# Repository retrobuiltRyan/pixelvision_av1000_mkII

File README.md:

# PixelVision_AV-1000_MkII

Desktop sized multi-format video display monitor for HDMI and legacy analog video input with built-in speakers.
Watch the video: (assembly section @14:51) <br>
 ## https://youtu.be/MTYouu-5v1Q <br> 
 <br>
## Hardware Overview

| Specification | Details |
|---|---|
| Viewable Size | 9.7” [4:3 ratio] |
| Input Signals | HDMI [2048×1536]; VGA [1920×1080]; YPbPr, S-video, Composite [480p] |
| Audio Input/Output | Analog 3.5mm stereo |
| Speaker Output | Stereo (5 watt) |
| Power Consumption | 10 watts (2w standby) |
| Dimensions (W × H × D) | 248 × 205 × 192 mm (9.76 × 8.07 × 7.56 inches) |
| Weight | 1350 g |

### IPS [iPad 3/4] Panel Details

| Specification | Details |
|---|---|
| Pixel Density | 264 PPI |
| View Angle | 89/89/89/89 (Typ.) (CR ≥ 10) |
| Frequency | 60 Hz |
| Panel Type / Model | a-Si TFT-LCD, LCM / LP097QX1-SPC1 |
| Brightness | 440 cd/m² |

## Electrical Diagram
 <br>

## Bill of Materials
| Item | Description | Vendor Link | Cost/each (USD) | Qty | Line Total (USD) |
|------|-------------|-------------|----------------:|----:|-----------------:|
| 1 alt | Speaker Dayton Audio CE32A-4 1-1/4" | [parts-express](https://www.parts-express.com/Dayton-Audio-CE32A-4-1-1-4-Mini-Speaker-4-Ohm-285-103) | 3.58 | 2 | $7.16 |
| 1 | Speaker Visaton FR7-4 2.5" | [parts-express](https://www.parts-express.com/Visaton-FR7-4-2-1-2-Full-Range-Driver-4-Ohm-292-638) | 6.47 | 2 | $12.94 |
| 2 | LCD 9.7" 2048×1536 HDMI | [aliexpress](https://www.aliexpress.us/item/3256803412961622.html) | 50.60 | 1 | $50.60 |
| 3 | Scan Line Converter | [aliexpress](https://www.aliexpress.us/item/3256805577379481.html) | 47.64 | 1 | $47.64 |
| 4 | M2.6 × 10mm Thread Forming Screw | [aliexpress]([#](https://www.aliexpress.us/item/3256807955659503.html)) | 0.04 | 70 | $2.80 |
| 5 | M3 × 6mm Button Head Screws | any | 0.03 | 3 | $0.09 |
| 6 | M3 × 11mm F/F Standoff | any | 0.10 | 3 | $0.30 |
| 7 | Filament, 1 gram PLA | any | 0.02 | 877 | $17.54 |
| 8 | Audio Amp PAM8406 | [aliexpress](https://www.aliexpress.us/item/3256807320222817.html) | 6.48 | 1 | $6.48 |
| 9 | M6 × 30 Steel Phillips Flat Head Screw | [mcmaster](https://www.mcmaster.com/91420A438/) | 0.13 | 1 | $0.13 |
| 10 | M6 Nylon Lock Nut | [mcmaster](https://www.mcmaster.com/90631A114/) | 0.08 | 1 | $0.08 |
| 11 | HDMI Super Slim Cable, 1 ft | [parts-express](https://www.parts-express.com/Audtek-TS1-1-ft.-Super-Slim-Ultra-HD-HDMI-2.0-Cable-4K60-Hz-HDR-YCbCr-444-18-Gbps-180-1318) | 3.97 | 1 | $3.97 |
| 12 | Audio Cable, Slim, 1 ft, 3.5mm | [parts-express](https://www.parts-express.com/3.5mm-Male-to-Male-Slim-Plug-Shielded-Audio-Cable-1-ft.-240-051) | 1.59 | 1 | $1.59 |
| 13 | DC Power Jack, Panel Mount (2.1 × 5.5mm) | [aliexpress](https://www.aliexpress.us/item/3256808307457555.html) | 0.45 | 2 | $0.90 |
| 14 | Rocker Switch panel mount (19 x 13mm) | [parts-express](https://www.parts-express.com/SPST-Miniature-Rocker-Switch-060-670) or [digikey](https://www.digikey.com/en/products/detail/e-switch/RA11131121/2720267) | 1.40 | 1 | $1.40 |
| 15 | Audio PCB (optional, but helpful) | custom DIY | 2.00 | 1 | $2.00 |
| 16 | Power PCB (optional, but helpful) | custom DIY | 3.00 | 1 | $3.00 |
| 17 | Rubber Feet (2 × 10mm), Round | [aliexpress](https://www.aliexpress.us/item/3256801658571146.html) | 0.10 | 4 | $0.40 |
| 18 | 12V 3A DC Power Supply (2.1 × 5.5mm) | [parts-express](https://www.parts-express.com/12V-DC-3A-AC-Adapter-Power-Supply-with-2.1-x-5.5mm-Center-Positive-Tip-with-Polarized-AC-Co-129-1204) | 7.00 | 1 | $7.00 |
| 19 | Perler Beads (plastic M2.5 washers) | any | 0.01 | 30 | $0.30 |
| 20 | Compression Spring, ~10mm OD, 25-35mm length, ~0.8mm wire dia, SS | any | 0.50 | 1 | 0.50|
| 21 | Electronics incidentals: wire, heat shrink, that one drop of hot glue | [any](#) | 1.00 | 1 | $1.00 |
| | **TOTAL** | | | | **$167.82** |

## Special Tools
You need a long reach (min 100mm) Torx T8 drive [like this](https://www.aliexpress.us/item/3256805848633499.html). If you source different M2.6 thread forming screws, then you need that matching (min 100mm long) bit drive tool .
 <br>

## 3D Printing 
These parts need to be printed. 15% infill, tree supports where applicable. <br>
*The two thin brackets that push the LCD against the front bezel are a mirrored pair. You need to clone + mirror in your slicer.* <br>

<br>

 *Critical Tip!* <br>  Absolutely block supports in blind screw holes. 

| Filament totals                              | Grams (g) | Cost/gram | Line total | Print time (hrs) |
|----------------------------------------------|----------:|----------:|-----------:|-----------------:|
| Body Rear                                    | 416       | $0.02     | $8.32      | 14               |
| Body Front Bezel                             | 146       |           | $2.92      | 3.75             |
| Yoke bulge                                   | 65        |           | $1.30      | 2.75             |
| LCD bracket                                  | 42        |           | $0.84      | 1                |
| Electronics Mount                            | 26        |           | $0.52      | 1                |
| IO panel                                     | 16        |           | $0.32      | 0.75             |
| Speaker, LCD brackets (x2) + buttons         | 36        |           | $0.72      | 1.55             |
| Swivel Base                                  | 130       |           | $2.60      | 5                |
| **Total**                                    | **877**   |           | **$17.54** | **29.8**         |

## PCBs 
(optional, but very helpful with internal wiring and matching the build shown in the video)

#### Fits this LCD panel (ipad 3/4 replacement screen):

## Support Me
If you want to support me and future work consider a [donation](https://www.paypal.com/donate/?hosted_button_id=JNT5P3N3XAK2E).
**You can also purchase a basic [fastener kit for this project](https://www.ebay.com/itm/147443247342).** This directly supports me, saves you some time sourcing parts, and clears out my surplus junk from the design process. 

<br>
Need a full-time hardware engineer? Hire me. DM me on twitter [@retrobuiltgames](https://x.com/retrobuiltgames)

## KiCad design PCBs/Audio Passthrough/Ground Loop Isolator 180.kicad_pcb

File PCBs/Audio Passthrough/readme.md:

Place all three kicad files (.kicad_pcb, .kicad_sch, .kicad_pro) in a folder of the same name. Open the project file (.kicad_pro) with KiCad.

- **2-in-1 PCB Application**
  - **Option 1:** TRS audio passthrough
  - **Option 2:** Ground loop isolator
  <br>

For the PixelVision AV-1000, we just need a simple 3.5mm TRS audio jack passthrough to reroute signals in the monitor enclosure. The bottom jumpers on the PCB must be soldered if this PCB is being used as a straight audio passthrough only. The board also doubles as a ground loop isolator using not-so-great audio transofrmers. (I use a ground loop isolator when I pull analog audio from a Raspberry Pi 3, which has some noisy analog audio.) From my 'raw ear listening' testing, you can't tell how the cheap these parts are. The 65mm diameter speakers cannot output freq under 100Hz, which doesnt matter as the cheap audio transformers cannot pass anything below 200Hz. That sub 200Hz roll-off numbers might be a lie one the datasheet- the parts are so cheap. 

 <br>
 <br>

 <br>

| Reference | Quantity | DigiKey P/N |
|-----------|---------:|-------------|
| J1, J2 | 2 | CP1-3523N-ND |

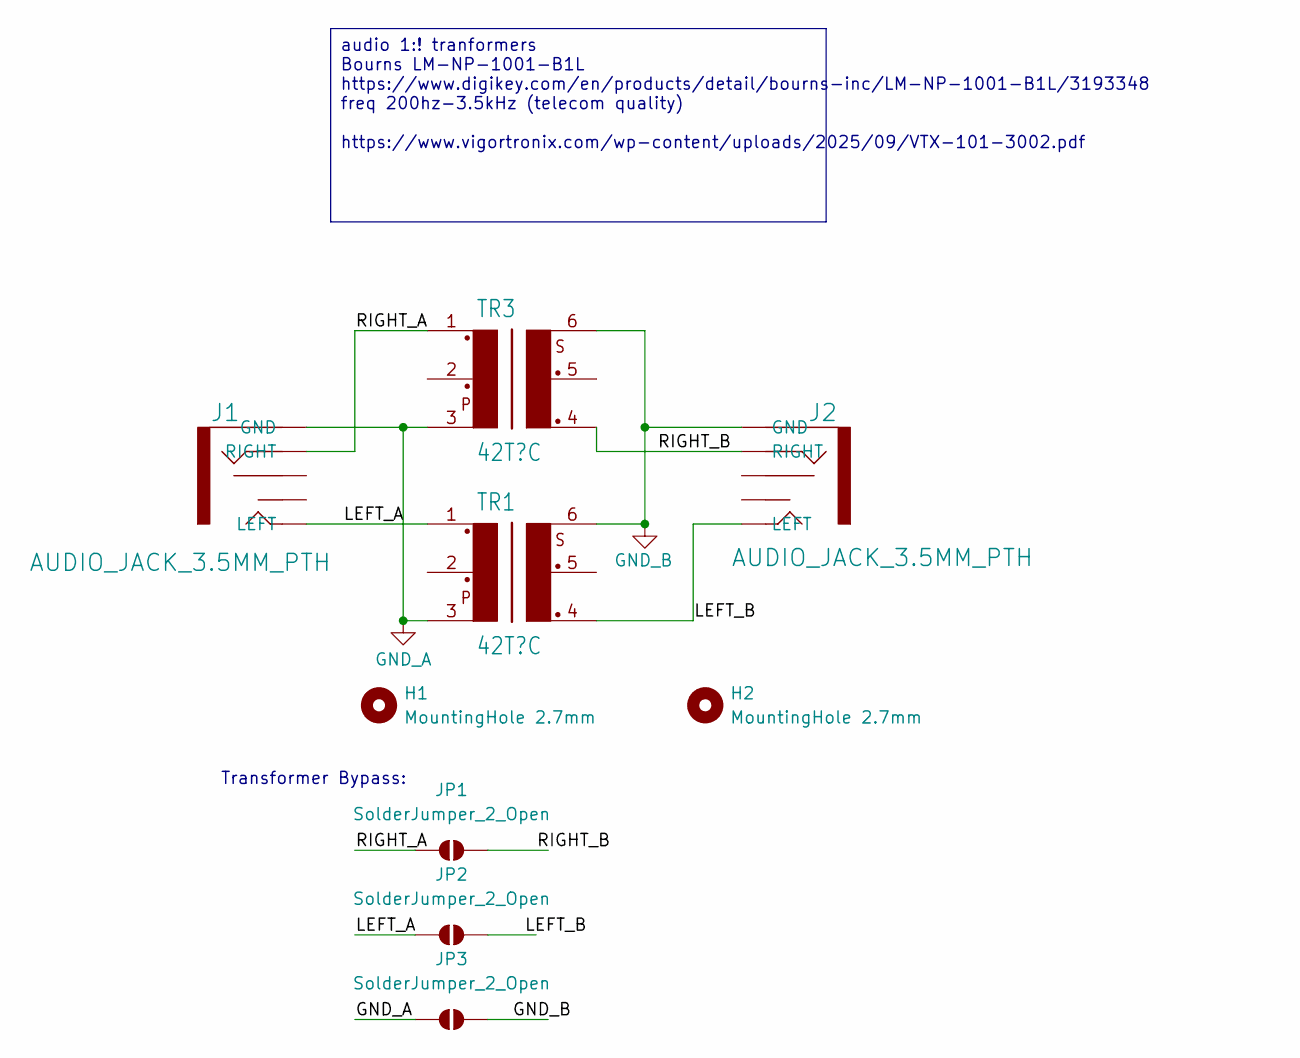
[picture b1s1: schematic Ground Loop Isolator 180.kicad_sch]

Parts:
H1, H2: MountingHole 2.7mm; MountingHole_2.7mm
J1, J2: AUDIO_JACK_3.5MM_PTH; AUDIO-JACK; DigiKey P/N CP1-3524NG-ND
JP1, JP2, JP3: SolderJumper_2_Open; SolderJumper-2_P2.7mm_Open_Pad2x1.5mm FAT
TR1, TR3: 42T?C; 42TC

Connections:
/LEFT_A: J1.LEFT, JP2.1 (A), TR1.1
/LEFT_B: J2.LEFT, JP2.2 (B), TR1.4
/RIGHT_A: J1.RIGHT, JP1.1 (A), TR3.1
/RIGHT_B: J2.RIGHT, JP1.2 (B), TR3.4
GND_A: J1.GND, JP3.1 (A), TR1.3, TR3.3
GND_B: J2.GND, JP3.2 (B), TR1.6, TR3.6

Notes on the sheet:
Transformer Bypass:
audio 1:! tranformers Bourns LM-NP-1001-B1L https://www.digikey.com/en/products/detail/bourns-inc/LM-NP-1001-B1L/3193348 freq 200hz-3.5kHz (telecom quality) https://www.vigortronix.com/wp-content/uploads/2025/09/VTX-101-3002.pdf

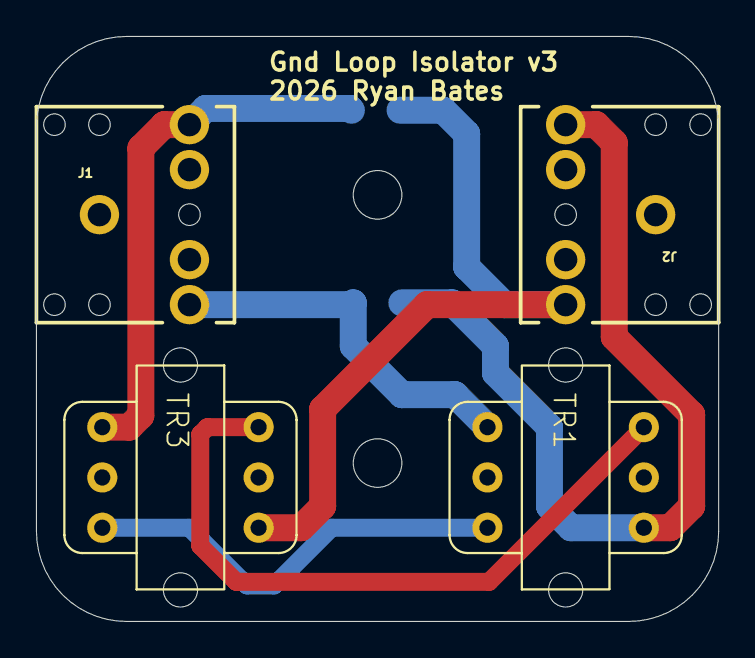
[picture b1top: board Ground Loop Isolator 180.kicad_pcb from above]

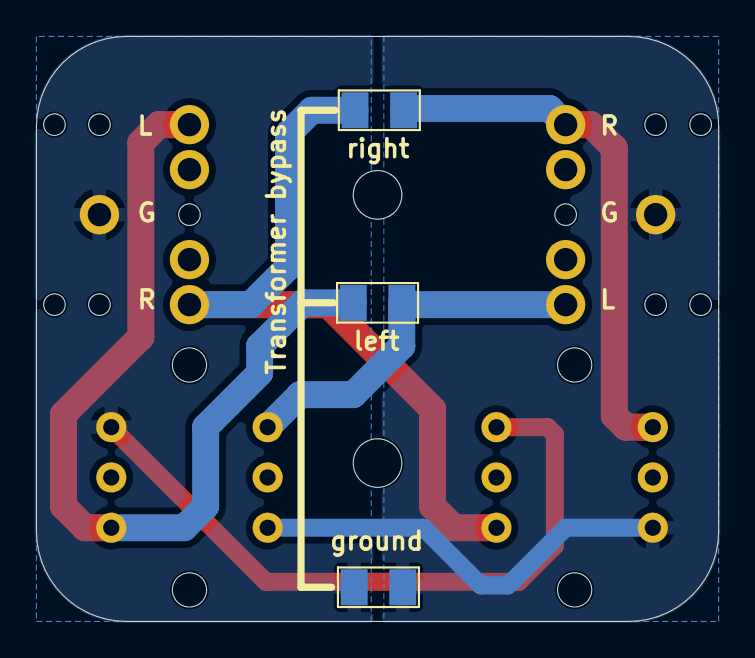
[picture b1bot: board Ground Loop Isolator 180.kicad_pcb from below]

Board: 2 copper layers, 37.9 x 32.5 mm, 9 parts (3 on the bottom side), 6 nets.

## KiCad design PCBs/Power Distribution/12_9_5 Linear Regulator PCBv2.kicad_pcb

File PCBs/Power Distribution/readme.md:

Place all three kicad files (.kicad_pcb, .kicad_sch, .kicad_pro) in a folder of the same name. Open the project file (.kicad_pro) with KiCad.

Handles input power distribution, power on/off switching, and power rerouting. Board includes two 5 V linear regulators and one adjustable buck converter.

 ## Bill of Materials
 | Reference | Value | Qty | DigiKey P/N |
|-----------|-------|----:|-------------|
| C1, C3, C5 | 0.22uF 50V CER | 3 | 445-2283-1-ND |
| C2, C4, C6 | 0.1uF 50V | 3 | 1276-1068-1-ND |
| D1 | DIODE STANDARD 50V 5A SMC | 1 | S5AC-FDICT-ND |
| J1, J2, J3, J4, J5, J6, J7 | Screw_Terminal_2_P3.50mm | 7 | 732-2747-ND |
| R3, R5, R6 | 330 | 3 | 311-330FRCT-ND |
| U2 | LM7809_TO220 | 1 | BA7809FP-E2CT-ND |
| U3 | L7805 | 1 | 497-7255-1-ND |
| U4 | Adj Buck Converter | 1 | [AliExpress](https://www.aliexpress.us/item/3256805684077964.html) |

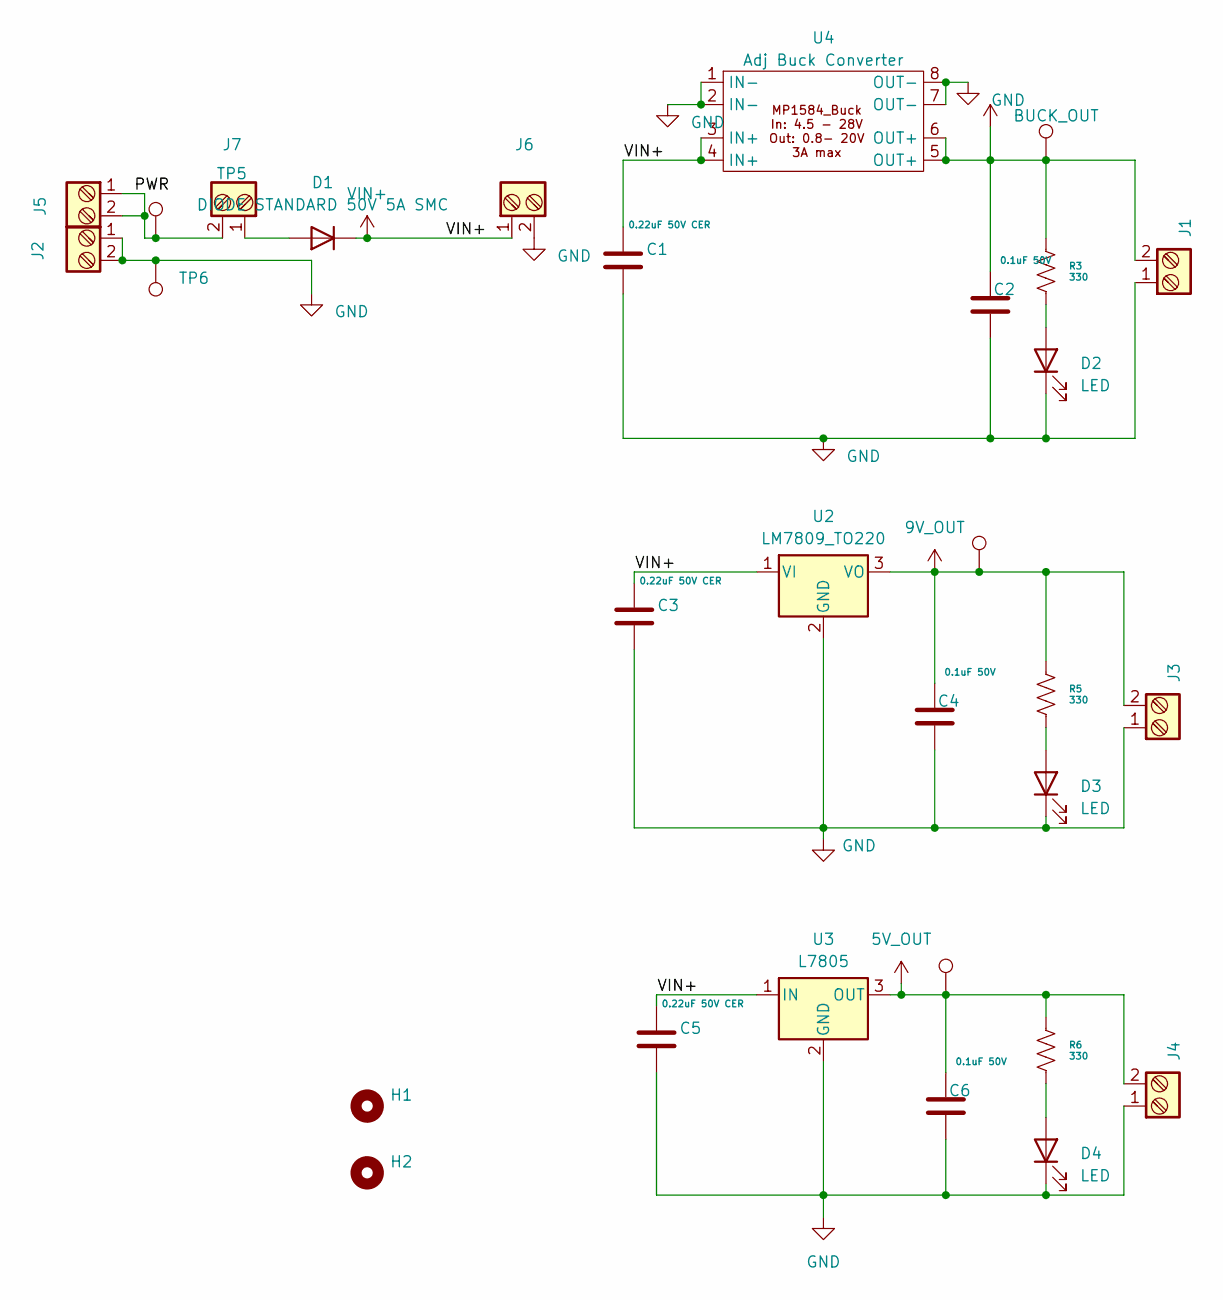
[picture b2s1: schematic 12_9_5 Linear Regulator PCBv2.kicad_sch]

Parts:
C1, C3, C5: 0.22uF 50V CER; C_1206_3216Metric; DigiKey P/N 445-2283-1-ND
C2, C4, C6: 0.1uF 50V; C_1206_3216Metric; DigiKey P/N 1276-1068-1-ND
D1: DIODE STANDARD 50V 5A SMC; D_SMC_Handsoldering; DigiKey P/N S5AC-FDICT-ND
D2, D3, D4: LED; LED_1206_3216Metric; DigiKey P/N 1080-1419-1-ND
H1, H2: MountingHole; MountingHole_3.2mm_M3
J1, J2, J3, J4, J5, J6, J7: Screw_Terminal_2_P3.50mm; TerminalBlock_Phoenix_PT-1,5-2-3.5-H_1x02_P3.50mm_Horizontal; DigiKey P/N 732-2747-ND
R3, R5, R6: 330; R_1206_3216Metric; DigiKey P/N 311-330FRCT-ND
TP1, TP3, TP4: uC +5V; TestPoint_Pad_2.0x2.0mm
TP5, TP6: TestPoint; TestPoint_Pad_2.5x2.5mm
U2: LM7809_TO220; TO-252-2; DigiKey P/N BA7809FP-E2CT-ND
U3: L7805; TO-252-2; DigiKey P/N 497-7255-1-ND
U4: Adj Buck Converter; MP1584

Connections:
5V_OUT: C6.1, J4.2, R6.1, TP4.1, U3.3 (OUT)
9V_OUT: C4.1, J3.2, R5.1, TP3.1, U2.3 (VO)
/PWR: J5.1, J5.2, J7.2, TP5.1
BUCK_OUT: C2.1, J1.2, R3.1, TP1.1, U4.5 (OUT+), U4.6 (OUT+)
GND: C1.2, C2.2, C3.2, C4.2, C5.2, C6.2, D2.1 (K), D3.1 (K), D4.1 (K), J1.1, J2.1, J2.2, J3.1, J4.1, J6.2, TP6.1, U2.2 (GND), U3.2 (GND), U4.1 (IN-), U4.2 (IN-), U4.7 (OUT-), U4.8 (OUT-)
unnamed: D1.2 (A), J7.1
unnamed: D2.2 (A), R3.2
unnamed: D3.2 (A), R5.2
unnamed: D4.2 (A), R6.2
VIN+: C1.1, C3.1, C5.1, D1.1 (K), J6.1, U2.1 (VI), U3.1 (IN), U4.3 (IN+), U4.4 (IN+)

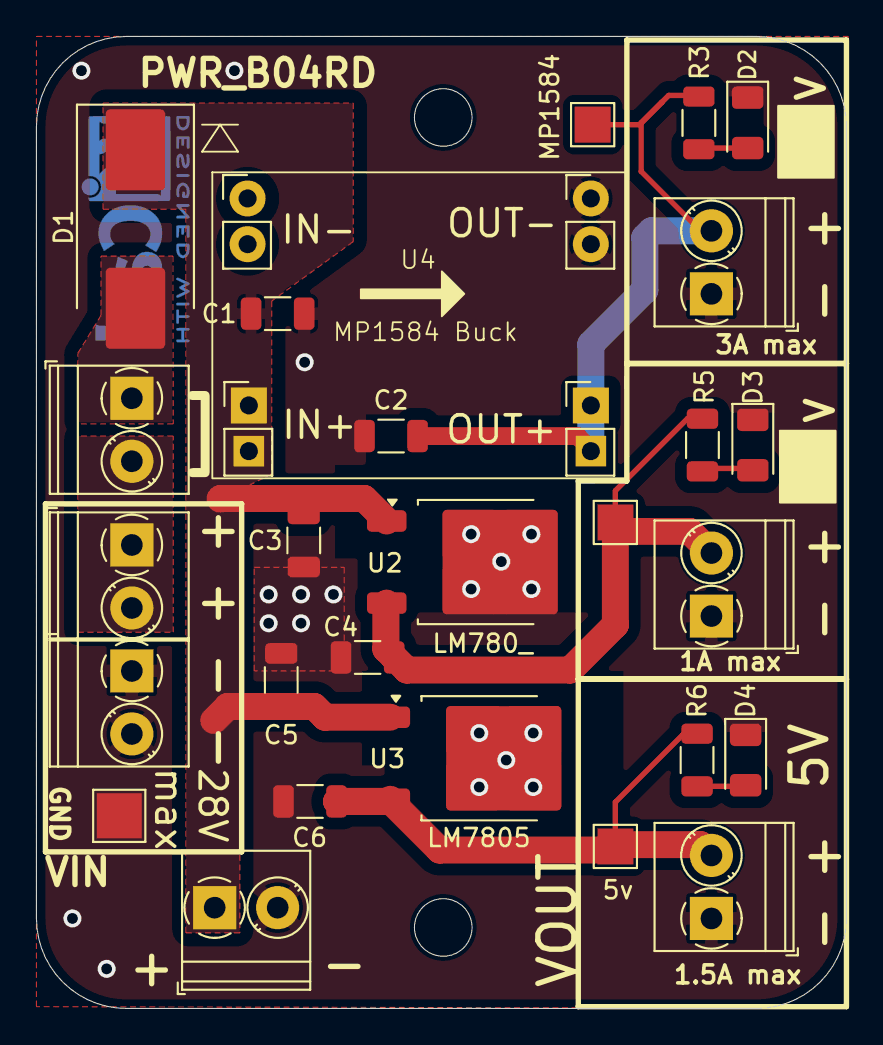
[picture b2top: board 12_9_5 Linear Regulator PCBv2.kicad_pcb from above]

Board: 2 copper layers, 45.0 x 54.0 mm, 29 parts (0 on the bottom side), 10 nets.

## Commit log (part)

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2026-06-22 Update README.md
    add BoM and Printing estimates
